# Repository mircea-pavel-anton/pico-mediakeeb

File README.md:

# pico-mediakeeb

A small multimedia macro-pad implemented on top of the RP2040 based Raspberry pi Pico.

---

## Getting Started

The basic steps to get this up and running are:

- Set up your Raspberry Pi Pico
- Order the PCB from your PCB printing service of choice
- Solder all the components to the PCB
- 3D print a case
- Assemble it all together

### Setting up your Pi

Setting up the Raspberry Pi Pico to function as the brains of this operation is a realtively simple 2-step task.

First things first. We need to flash our Pi with the latest CircuitPython uf2 file so that we can use micropython to program it and gain access to useful adafruit libraries.

You can find the latest CircuitPython.uf2 file as well as a flashing guide [here](https://learn.adafruit.com/getting-started-with-raspberry-pi-pico-circuitpython/circuitpython)

Once you flashed your pico, it should unmount by itself and then remount as a storage device called `CIRCUITPYTHON`. That means you succesfully flashed your pi and are ready to continue.  

Next, we need to download or clone this repo, and copy over the contents of `src/` into the mounted `CIRCUITPYTHON` volume, so thy pi can run it. Once you copied everything over, the pi should start running the code. You can tell whether or not it is working by the onboard LED. Once the program starts running, it should turn on. If it doesn't, try unplugging and replugging your pico.

### Printing your own PCB

| PCB Front | PCB Back |
| :-------: | :------: |
|  |  |

In the `pcb/` directory of this repo, you can find a KiCAD project that contains the circuit schematic (in case you want to handwire everything) and a PCB design (in case you want to print your own board). You should open the project and generate the gerber files, or just take the pre-generated ones from `pcb/gerber` and send them to your preffered PCB printing service. I personally used JLC PCB.

### Soldering the components to the PCB

The components you need for this project are the following:

- A raspberry pi Pico
- 2 10k ohm resistors
- a rotary encoder with a switch
- 6 cherry-style keyswitches

All the part names are printed onto the PCB, so you should have no issues in finding out what to solder where.

### 3D printing a case

TODO ...

### Assemble it all together

TODO ...

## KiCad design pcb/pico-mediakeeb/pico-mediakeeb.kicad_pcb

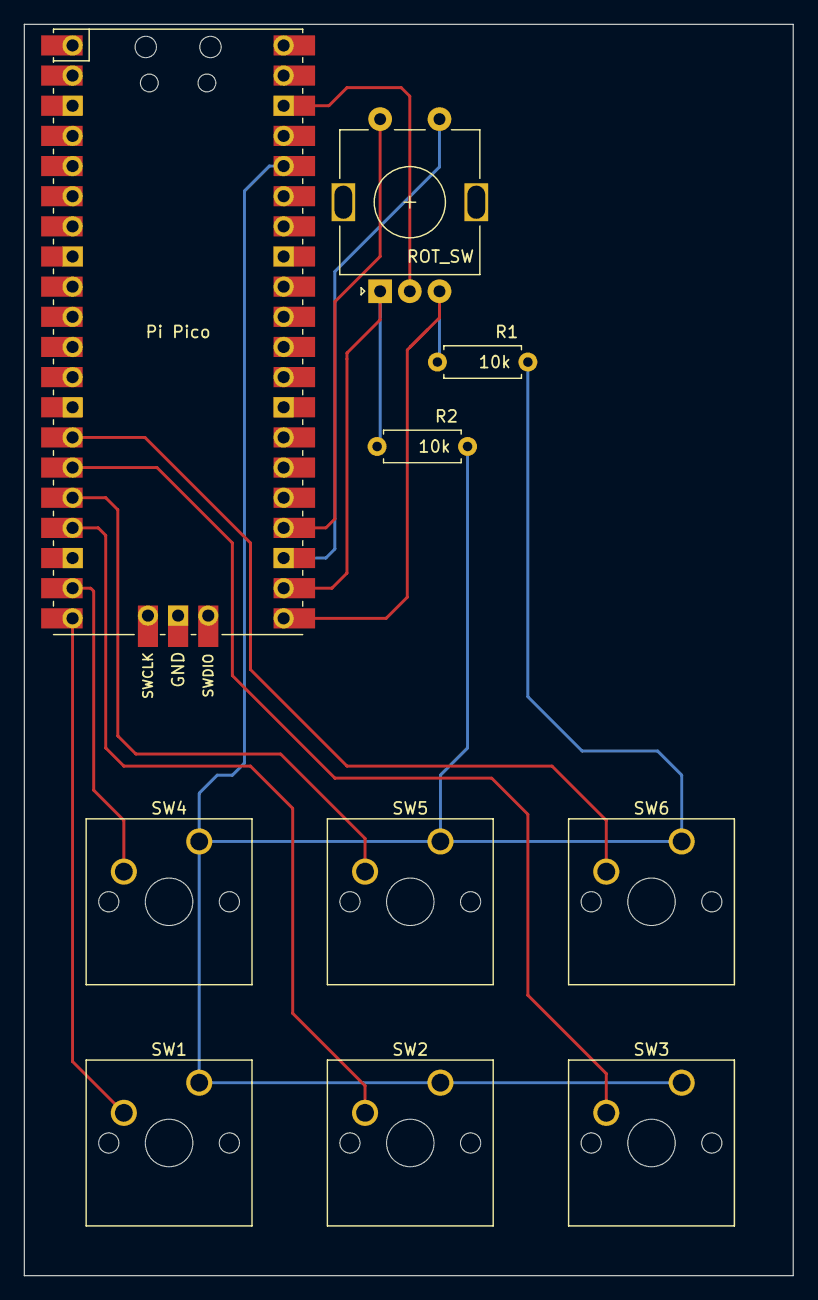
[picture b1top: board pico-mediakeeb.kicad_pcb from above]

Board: 2 copper layers, 64.8 x 105.4 mm, 10 parts (0 on the bottom side), 12 nets.

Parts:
Pi Pico: RPi_Pico_SMD_TH
R1, R2: 10k; R_Axial_DIN0207_L6.3mm_D2.5mm_P7.62mm_Horizontal
ROT_SW: Rotary_Encoder_Switch; RotaryEncoder_Alps_EC11E-Switch_Vertical_H20mm
SW1: btn_prev; SW_Cherry_MX_1.00u_PCB
SW2: btn_play_pause; SW_Cherry_MX_1.00u_PCB
SW3: btn_next; SW_Cherry_MX_1.00u_PCB
SW4: btn_macro_1; SW_Cherry_MX_1.00u_PCB
SW5: btn_macro_2; SW_Cherry_MX_1.00u_PCB
SW6: btn_macro_3; SW_Cherry_MX_1.00u_PCB

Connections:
unnamed: Pi Pico.36, R1.1, R2.1, SW1.1, SW2.1, SW3.1, SW4.1, SW5.1, SW6.1
unnamed: Pi Pico.21, R1.2, ROT_SW.B
unnamed: Pi Pico.22, R2.2, ROT_SW.A
unnamed: Pi Pico.20, SW1.2
unnamed: Pi Pico.17, SW2.2
unnamed: Pi Pico.15, SW3.2
unnamed: Pi Pico.19, SW4.2
unnamed: Pi Pico.16, SW5.2
unnamed: Pi Pico.14, SW6.2
unnamed: Pi Pico.38, ROT_SW.C
unnamed: Pi Pico.23, ROT_SW.S1
unnamed: Pi Pico.24, ROT_SW.S2

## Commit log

2021-05-04 Import the adafruit_hid library
2021-05-04 Rename the pico board to `pico-mediakeeb`
2021-05-04 Set custom boot script to bind bootsel on GP0
2021-05-04 Implement basic multimedia functionality
2021-05-04 Move all code under `src/`
2021-05-04 Add 3 more macro buttons
2021-05-05 Create gitignore
2021-05-05 Restructure project
2021-05-05 Create custom class for buttons
2021-05-05 Create custom class for rotary encoders
2021-05-05 Create custom class for leds
2021-05-05 Define all multimedia functions
2021-05-05 Implement custom classes
2021-05-05 Fix typo in README
2021-05-05 Move all source code files into the `src/` dir
2021-05-05 Create kicad Project
2021-05-05 Change button pins
2021-05-05 change pin order
2021-05-05 Add circuit schematic
2021-05-05 Make labels more readable
2021-05-05 Change pins
2021-05-05 Update schematic to use generic rotary encoder
2021-05-05 Remove unused lib
2021-05-05 Update schematic
2021-05-05 Auto generate PCB
2021-05-07 Update pcb design
2021-05-07 Change pinout
2021-05-11 Reorder buttons to make more sense for the pcb design
2021-05-11 Implement pcb design v1
2021-05-11 Update code to reflect button pin changes
2021-05-11 Upload PCB screenshots
2021-05-11 Add pcb screenshots
2021-05-11 Properly allign screenshots
2021-05-11 Add gerber files
2021-05-16 Update pcb traces and add JLC order number placeholder
2021-05-16 Update gerber files
2022-02-01 [ImgBot] Optimize images
    *Total -- 198.81kb -> 119.53kb (39.87%)
    /res/pcb-back.png -- 92.08kb -> 51.34kb (44.24%)
    /res/pcb-front.png -- 106.73kb -> 68.19kb (36.1%)
2022-02-01 [ImgBot] Optimize images (#1)
    *Total -- 198.81kb -> 119.53kb (39.87%)
    /res/pcb-back.png -- 92.08kb -> 51.34kb (44.24%)
    /res/pcb-front.png -- 106.73kb -> 68.19kb (36.1%)

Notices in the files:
pcb/pico-mediakeeb/pico-mediakeeb.kicad_pcb:
Licence: GPL-v3.0
